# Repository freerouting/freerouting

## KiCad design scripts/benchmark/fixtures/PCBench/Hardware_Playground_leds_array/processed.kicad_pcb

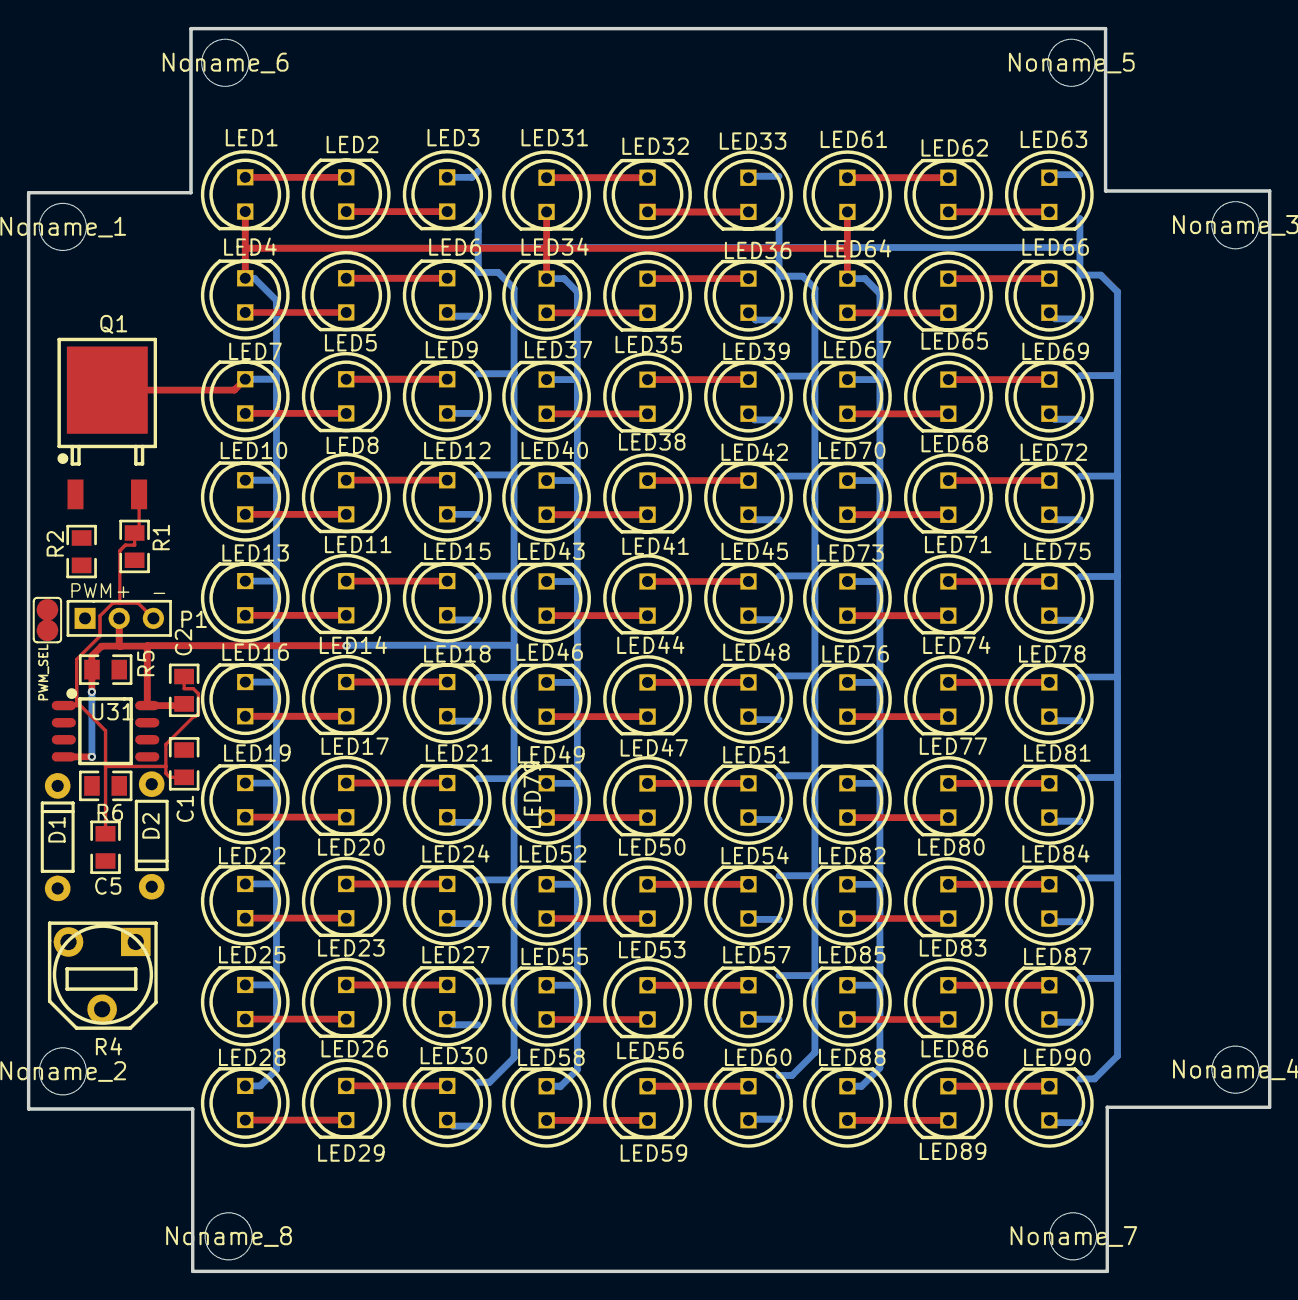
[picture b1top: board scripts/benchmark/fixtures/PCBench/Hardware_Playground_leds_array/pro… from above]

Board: 2 copper layers, 92.2 x 92.3 mm, 142 parts (0 on the bottom side), 93 nets.

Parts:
C1, C2: 100n; 0805
C5: 1n; 0805
D1, D2: 1N4148TA; DO-35
LED1, LED2, LED3, LED4, LED5, LED6, LED7, LED8, LED9, LED10, LED11, LED12, LED13, LED14, LED15, LED16, LED17, LED18, LED19, LED20, LED21, LED22, LED23, LED24, LED25, LED26, LED27, LED28, LED29, LED30, LED31, LED32, LED33, LED34, LED35, LED36, LED37, LED38, LED39, LED40, LED41, LED42, LED43, LED44, LED45, LED46, LED47, LED48, LED49, LED50, LED51, LED52, LED53, LED54, LED55, LED56, LED57, LED58, LED59, LED60, LED61, LED62, LED63, LED64, LED65, LED66, LED67, LED68, LED69, LED70, LED71, LED72, LED73, LED74, LED75, LED76, LED77, LED78, LED79, LED80, LED81, LED82, LED83, LED84, LED85, LED86, LED87, LED88, LED89, LED90: 5AG3HT01 280-450; LED-5MM
Noname_1, Noname_2, Noname_3, Noname_4, Noname_5, Noname_6, Noname_7, Noname_8: MountingHole_3.50mm
P1: Header-Female-2.54_1x3; HDR-3X1_2.54
PWM_SEL: SJ
Q1: IRLR024NTRPBF; TO-252-2
R1: 10K; 0805
R2: 100; 0805
R4: 10K; RM065-V1
R5, R6: 1K; 0805
U1, U2, U3, U4, U5, U6, U7, U8, U9, U10, U11, U12, U13, U14, U15, U16, U17, U18, U19, U20, U21, U22, U23, U24, U25, U26, U27, U28, U29, U30: NSI45020T1G; SOD-123F
U31: NE555G-S08-R; SOP-8_150MIL

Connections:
A: C2.1, P1.2, R5.2, U1.1, U2.1, U3.1, U4.1, U5.1, U6.1, U7.1, U8.1, U9.1, U10.1, U11.1, U12.1, U13.1, U14.1, U15.1, U16.1, U17.1, U18.1, U19.1, U20.1, U21.1, U22.1, U23.1, U24.1, U25.1, U26.1, U27.1, U28.1, U29.1, U30.1, U31.4, U31.8
GND: C1.1, C2.2, C5.1, P1.3, Q1.3, R1.1, U31.1
K: LED1.2, LED4.2, LED7.2, LED10.2, LED13.2, LED16.2, LED19.2, LED22.2, LED25.2, LED28.2, LED31.2, LED34.2, LED37.2, LED40.2, LED43.2, LED46.2, LED49.2, LED52.2, LED55.2, LED58.2, LED61.2, LED64.2, LED67.2, LED70.2, LED73.2, LED76.2, LED79.2, LED82.2, LED85.2, LED88.2, Q1.4
LED1_1: LED1.1, LED2.2
LED2_1: LED2.1, LED3.2
LED3_1: LED3.1, U1.2
LED4_1: LED4.1, LED5.2
LED5_1: LED5.1, LED6.2
LED6_1: LED6.1, U2.2
LED7_1: LED7.1, LED8.2
LED8_1: LED8.1, LED9.2
LED9_1: LED9.1, U3.2
LED10_1: LED10.1, LED11.2
LED11_1: LED11.1, LED12.2
LED12_1: LED12.1, U4.2
LED13_1: LED13.1, LED14.2
LED14_1: LED14.1, LED15.2
LED15_1: LED15.1, U5.2
LED16_1: LED16.1, LED17.2
LED17_1: LED17.1, LED18.2
LED18_1: LED18.1, U6.2
LED19_1: LED19.1, LED20.2
LED20_1: LED20.1, LED21.2
LED21_1: LED21.1, U7.2
LED22_1: LED22.1, LED23.2
LED23_1: LED23.1, LED24.2
LED24_1: LED24.1, U8.2
LED25_1: LED25.1, LED26.2
LED26_1: LED26.1, LED27.2
LED27_1: LED27.1, U9.2
LED28_1: LED28.1, LED29.2
LED29_1: LED29.1, LED30.2
LED30_1: LED30.1, U10.2
LED31_1: LED31.1, LED32.2
LED32_1: LED32.1, LED33.2
LED33_1: LED33.1, U11.2
LED34_1: LED34.1, LED35.2
LED35_1: LED35.1, LED36.2
LED36_1: LED36.1, U12.2
LED37_1: LED37.1, LED38.2
LED38_1: LED38.1, LED39.2
LED39_1: LED39.1, U13.2
LED40_1: LED40.1, LED41.2
LED41_1: LED41.1, LED42.2
LED42_1: LED42.1, U14.2
LED43_1: LED43.1, LED44.2
LED44_1: LED44.1, LED45.2
LED45_1: LED45.1, U15.2
LED46_1: LED46.1, LED47.2
LED47_1: LED47.1, LED48.2
LED48_1: LED48.1, U16.2
LED49_1: LED49.1, LED50.2
LED50_1: LED50.1, LED51.2
LED51_1: LED51.1, U17.2
LED52_1: LED52.1, LED53.2
LED53_1: LED53.1, LED54.2
LED54_1: LED54.1, U18.2
LED55_1: LED55.1, LED56.2
LED56_1: LED56.1, LED57.2
LED57_1: LED57.1, U19.2
LED58_1: LED58.1, LED59.2
LED59_1: LED59.1, LED60.2
LED60_1: LED60.1, U20.2
LED61_1: LED61.1, LED62.2
LED62_1: LED62.1, LED63.2
LED63_1: LED63.1, U21.2
LED64_1: LED64.1, LED65.2
LED65_1: LED65.1, LED66.2
LED66_1: LED66.1, U22.2
LED67_1: LED67.1, LED68.2
LED68_1: LED68.1, LED69.2
LED69_1: LED69.1, U23.2
LED70_1: LED70.1, LED71.2
LED71_1: LED71.1, LED72.2
LED72_1: LED72.1, U24.2
LED73_1: LED73.1, LED74.2
LED74_1: LED74.1, LED75.2
LED75_1: LED75.1, U25.2
LED76_1: LED76.1, LED77.2
LED77_1: LED77.1, LED78.2
LED78_1: LED78.1, U26.2
LED79_1: LED79.1, LED80.2
LED80_1: LED80.1, LED81.2
LED81_1: LED81.1, U27.2
LED82_1: LED82.1, LED83.2
LED83_1: LED83.1, LED84.2
LED84_1: LED84.1, U28.2
LED85_1: LED85.1, LED86.2
LED86_1: LED86.1, LED87.2
LED87_1: LED87.1, U29.2
LED88_1: LED88.1, LED89.2
LED89_1: LED89.1, LED90.2
LED90_1: LED90.1, U30.2

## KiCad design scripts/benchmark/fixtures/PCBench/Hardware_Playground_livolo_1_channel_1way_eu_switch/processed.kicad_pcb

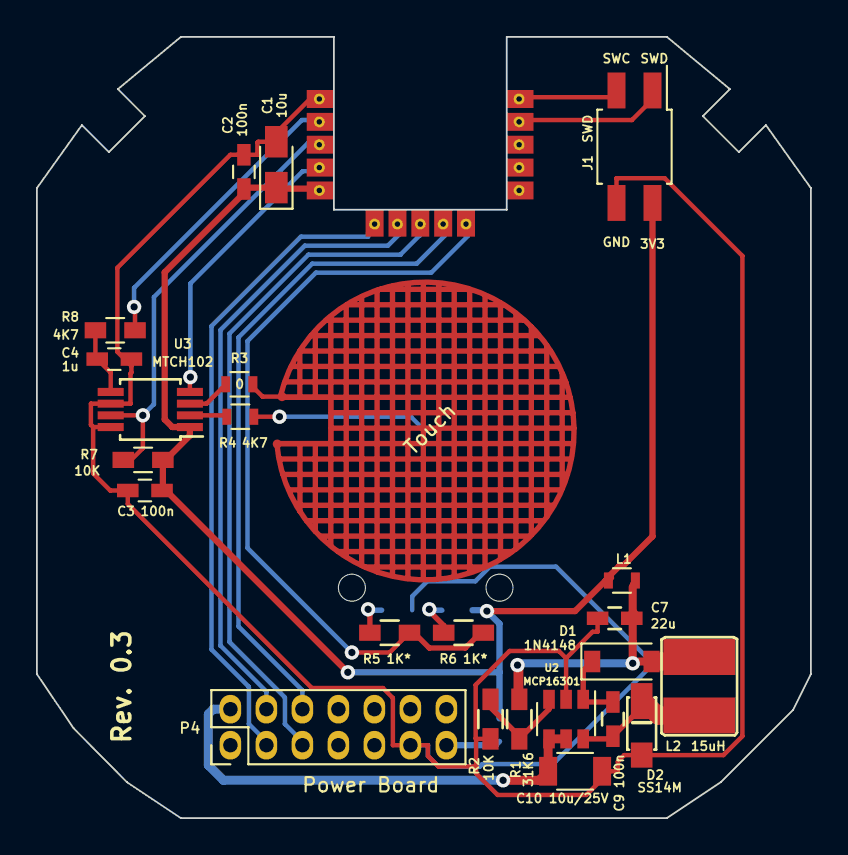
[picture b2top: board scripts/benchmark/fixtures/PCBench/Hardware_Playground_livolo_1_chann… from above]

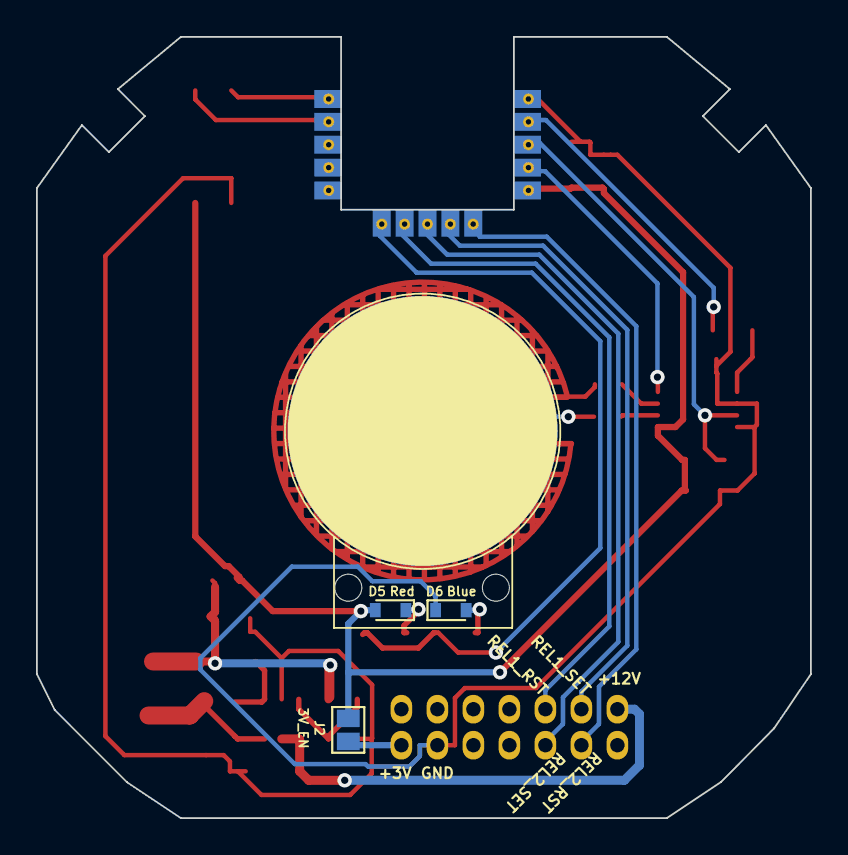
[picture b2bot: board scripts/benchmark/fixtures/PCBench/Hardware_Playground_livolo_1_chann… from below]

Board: 2 copper layers, 43.0 x 43.4 mm, 28 parts (4 on the bottom side), 25 nets.

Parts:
C1: 10u; CP_Tantalum_Case-R_EIA-2012-12_Wave
C2, C3, C9: 100n; C_0603_HandSoldering
C4: 1u; C_0603_HandSoldering
C7: 22u; C_0603_HandSoldering
C10: 10u/25V; C_1206
D1: 1N4148; SOD-123
D2: SS14M
D5: Red; D_0603
D6: Blue; D_0603
J1: SWD; Pin_Header_Straight_2x02_Pitch2.00mm_SMD
J2: 3V_EN; GS2
L1: BLM18HE152SN1D; R_0603
L2: 15uH; VLCF4020T-150MR68
P4: Power Board; Pin_Header_Straight_2x07_Pitch2.00mm
R1: 31K6; R_0603_HandSoldering
R2, R7: 10K; R_0603_HandSoldering
R3: 0; R_0603
R4: 4K7; R_0603
R5, R6: 1K*; R_0603_HandSoldering
R8: 4K7; R_0603_HandSoldering
U1: Touch; livolo_ts_guard
U2: MCP16301; SOT-23-6
U3: MTCH102; MSOP-8_3x3mm_Pitch0.65mm
U5: H_NRF52832; Holyiot-NRF52832

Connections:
+3V3: C1.1, C2.2, C3.2, D5.2, J1.2, J2.1, L1.2, R7.2, U3.1, U5.5
/12Vcc: C10.1, P4.2, U2.4, U2.5
/MTPM: U3.4, U5.4
/MTSA: R8.1, U5.2
/Relay1_Reset: P4.6, U5.9
/Relay1_Set: P4.4, U5.7
/Relay2_Reset: P4.3, U5.6
/Relay2_Set: P4.5, U5.8
/S1_LEDs: R5.2, R6.2, U5.10
/SWCLK: J1.3, U5.15
/SWDIO: J1.1, U5.14
/TS1: R7.1, U3.7, U5.3
GND: C1.2, C2.1, C3.1, C4.2, C7.2, C10.2, D2.2, D6.1, J1.4, P4.11, R2.1, U2.2, U3.6, U3.8, U5.1
unnamed: C4.1, R8.2, U3.5
unnamed: C7.1, D1.2, L1.1, L2.1, R1.2
unnamed: C9.1, D1.1, U2.1
unnamed: C9.2, D2.1, L2.2, U2.6
unnamed: D5.1, R6.1
unnamed: D6.2, R5.1
unnamed: J2.2, P4.13
unnamed: R1.1, R2.2, U2.3
unnamed: R3.1, U3.3
unnamed: R3.2, U1.2
unnamed: R4.1, U3.2
unnamed: R4.2, U1.1

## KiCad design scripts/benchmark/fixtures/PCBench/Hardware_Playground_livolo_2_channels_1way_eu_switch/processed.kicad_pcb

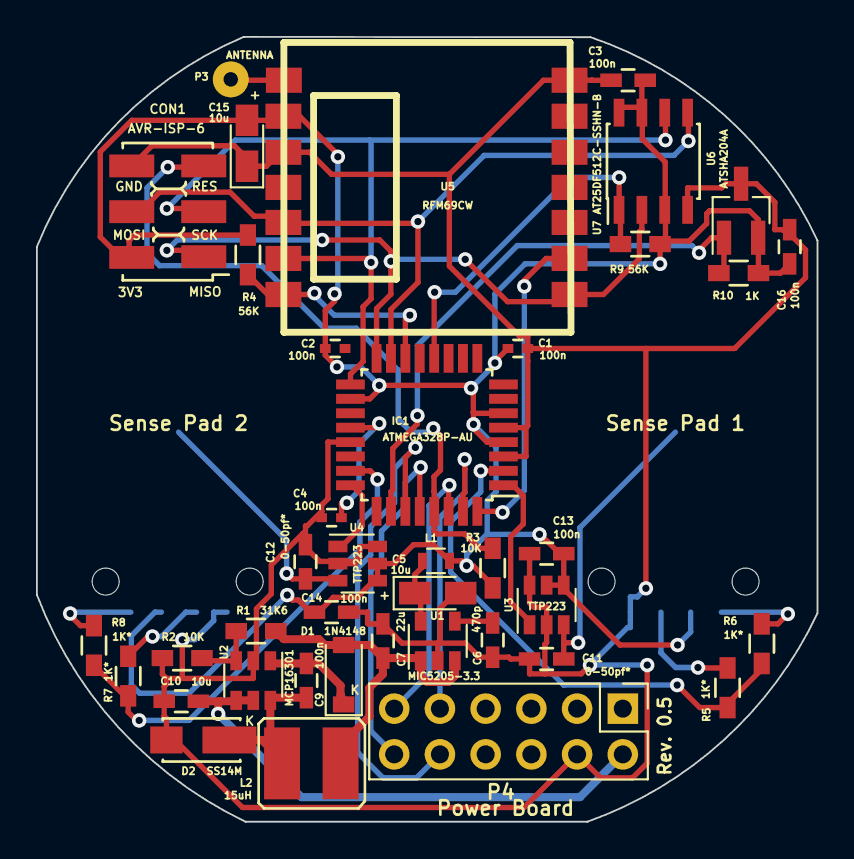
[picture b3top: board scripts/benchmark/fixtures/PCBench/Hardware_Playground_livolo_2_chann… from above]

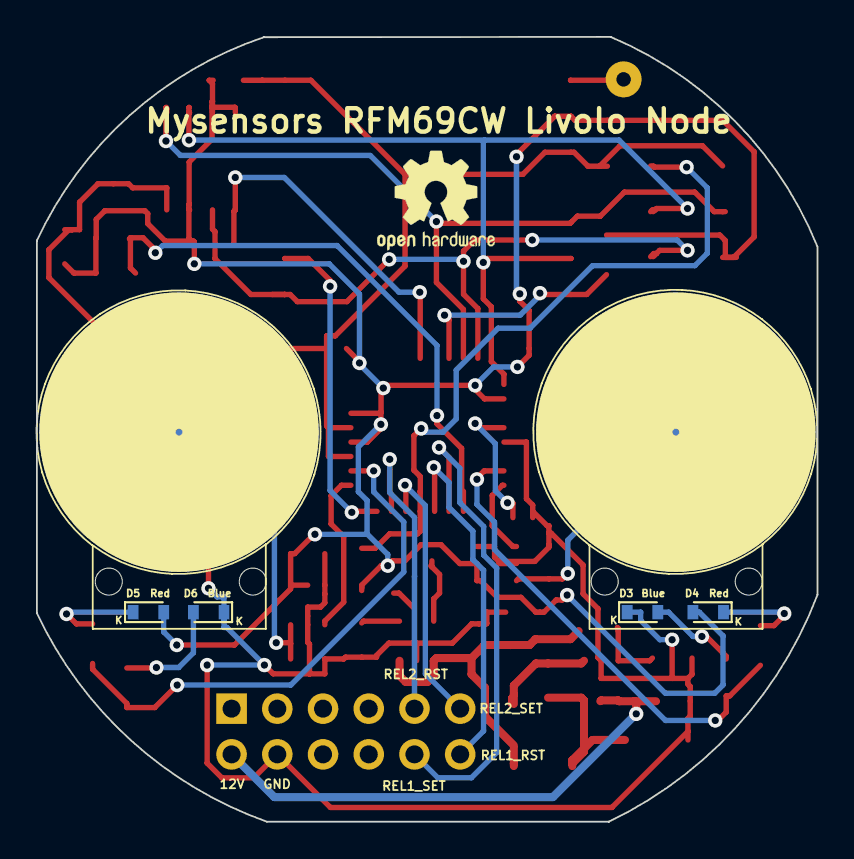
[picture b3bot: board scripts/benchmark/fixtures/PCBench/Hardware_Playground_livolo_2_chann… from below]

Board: 2 copper layers, 43.4 x 43.6 mm, 46 parts (4 on the bottom side), 33 nets.

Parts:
C1, C2, C4: 100n; C_0402
C3, C9, C13, C14, C16: 100n; C_0603_HandSoldering
C5, C15: 10u; CP_Tantalum_Case-R_EIA-2012-12_Wave
C6: 470p; C_0603_HandSoldering
C7: 22u; C_0603_HandSoldering
C10: 10u; C_0603_HandSoldering
C11, C12: 0-50pf*; C_0603_HandSoldering
CON1: AVR-ISP-6; AVR_ISP_SMT_Small_02x03
D1: 1N4148; SOD-123
D2: SS14M
D3, D6: Blue; D_0603
D4, D5: Red; D_0603
IC1: ATMEGA328P-AU; TQFP-32_7x7mm_Pitch0.8mm
L1: BLM18HE152SN1D; R_0603
L2: 15uH; VLCF4020T-150MR68
P1: Sense Pad 1; touch_pad_16mm
P2: Sense Pad 2; touch_pad_16mm
P3: ANTENNA; SolderWirePad_single_0-8mmDrill
P4: Power Board; Pin_Header_Straight_2x06_Pitch2.54mm
R1: 31K6; R_0603_HandSoldering
R2, R3: 10K; R_0603_HandSoldering
R4, R9: 56K; R_0603_HandSoldering
R5, R6, R7, R8: 1K*; R_0603_HandSoldering
R10: 1K; R_0603_HandSoldering
U1: MIC5205-3.3; SOT-23-5
U2: MCP16301; SOT-23-6
U3, U4: TTP223; SOT-23-6
U5: RFM69CW
U6: AT25DF512C-SSHN-B; SOIC-8_3.9x4.9mm_Pitch1.27mm
U7: ATSHA204A; SOT-23_Handsoldering

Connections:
+3V3: C1.1, C2.2, C3.2, C13.1, C14.1, C15.2, C16.2, CON1.2, D4.2, D5.2, IC1.4, IC1.6, IC1.18, L1.1, R3.1, R4.2, R9.1, R10.1, U3.4, U3.5, U4.4, U4.5, U5.2, U6.3, U6.7, U6.8, U7.2
/12Vcc: C10.1, P4.2, U2.4, U2.5
/ATSHA204A: IC1.26, R10.2, U7.1
/FLASH_SS: IC1.12, R9.2, U6.1
/INT: IC1.32, U5.9
/MISO: CON1.1, IC1.16, U5.8, U6.2
/MOSI: CON1.4, IC1.15, U5.5, U6.5
/RADIO_SS: IC1.14, R4.1, U5.7
/RESET: CON1.5, IC1.29, R3.2
/Relay1_Reset: IC1.28, P4.12
/Relay1_Set: IC1.27, P4.10
/Relay2_Reset: IC1.31, P4.9
/Relay2_Set: IC1.30, P4.11
/S1_LEDs: IC1.2, R5.2, R6.2
/S2_LEDs: IC1.23, R7.2, R8.2
/SCK: CON1.3, IC1.17, U5.6, U6.6
/TS1: IC1.1, U3.1
/TS2: IC1.24, U4.1
GND: C1.2, C3.1, C4.1, C5.2, C6.2, C7.2, C10.2, C11.2, C12.2, C13.2, C14.2, C15.1, C16.1, CON1.6, D2.2, D3.1, D6.1, IC1.3, IC1.5, IC1.21, P4.4, R2.1, U1.2, U2.2, U3.2, U3.6, U4.2, U4.6, U5.3, U5.14, U6.4, U7.3
unnamed: C4.2, IC1.20
unnamed: C5.1, L1.2, U1.5
unnamed: C6.1, U1.4
unnamed: C7.1, D1.2, L2.1, R1.2, U1.1, U1.3
unnamed: C9.1, D1.1, U2.1
unnamed: C9.2, D2.1, L2.2, U2.6
unnamed: C11.1, P1.1, U3.3
unnamed: C12.1, P2.1, U4.3
unnamed: D3.2, R7.1
unnamed: D4.1, R8.1
unnamed: D5.1, R6.1
unnamed: D6.2, R5.1
unnamed: P3.1, U5.1
unnamed: R1.1, R2.2, U2.3
